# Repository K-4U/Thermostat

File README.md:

Thermostat
==========

This project will be able to replace a standard Thermostat hanging on your wall. The project is **not** suitable for [OpenTherm](http://en.wikipedia.org/wiki/OpenTherm "OpenTherm").

For now, the project is only an idea.

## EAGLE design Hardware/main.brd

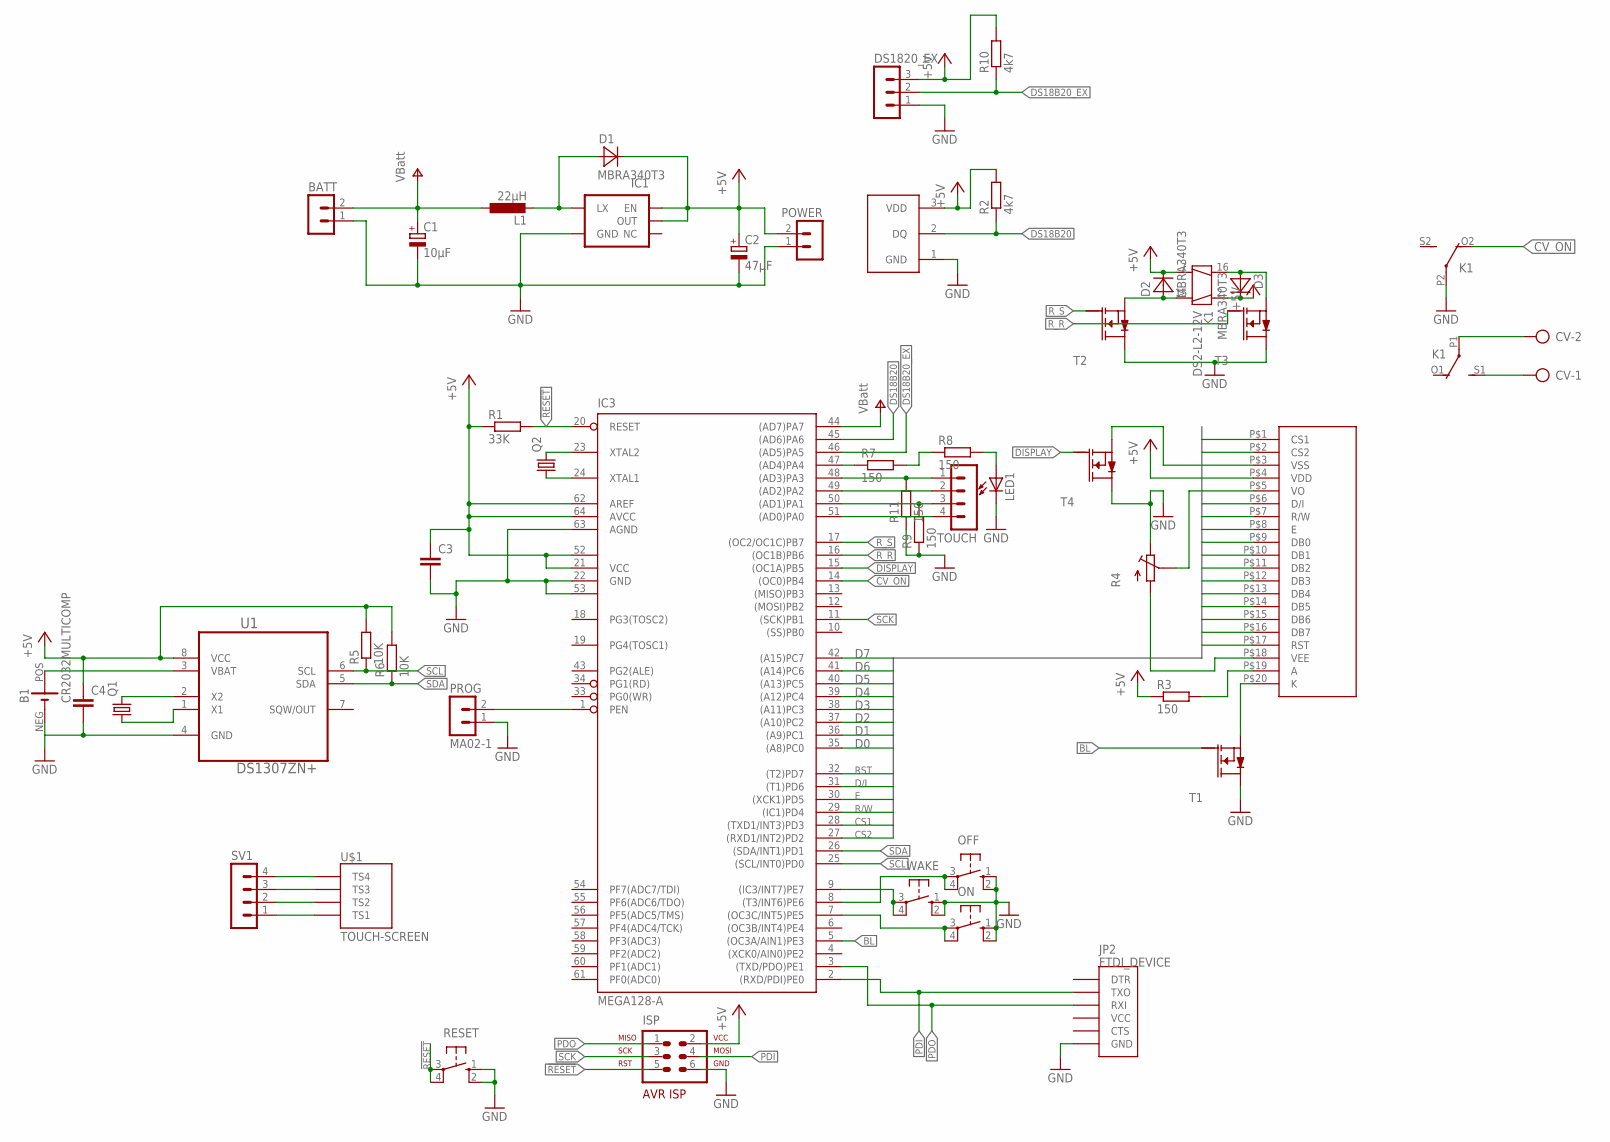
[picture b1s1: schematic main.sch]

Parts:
B1: CR2032MULTICOMP; CR2032
BATT: MA02-1
C1: 10µF; PANASONIC_D
C2: 47µF; PANASONIC_D
C3, C4: C-EUC0805; C0805
CV: AK300/2
D1, D2, D3: MBRA340T3; SMA
DS1820: DS18B20; TO92
DS1820_EX: MA03-1
IC1: V_REG_NCP1400SOT23-5; SOT23-5
IC3: MEGA128-A; TQFP64
ISP: AVR-ISP-6HORZ; AVR-ISP-6R
JP2: FTDI_DEVICE; FTDI_DEVICE_SIDE
K1: DS2-L2-12V; DS2E-L2
L1: 22µH; L2012C
LED1: LEDSML1206; SML1206
OFF: 10-XX; B3F-10XX
ON: 10-XX; B3F-10XX; MPN B3F-1000
POWER: MA02-1
PROG: MA02-1
Q1: CRYSTALTC26V; TC26V
Q2: CRYSTALSM49; SM49
R1: 33K; R0805
R2, R10: 4k7; R0805
R3, R7, R8, R9, R11: 150; R0805
R4: TRIM
R5, R6: 10K; R0805
RESET: 10-XX; B3F-10XX
SV1: MA04-1
T1, T2, T3, T4: IRLML2502PBF; SOT23
TOUCH: MA04-1
U1: DS1307ZN+; SOIC127P600X175-8N
U$1: TOUCH-SCREEN
U$2: GLCD_LEDSEE
WAKE: 10-XX; B3F-10XX

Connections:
!RESET: IC3.20 (RESET), ISP.5, R1.2, RESET.3, RESET.4 (P1)
+5V: C2.+, C3.1, C4.1, D1.C, D2.C, D3.C, DS1820.3 (VDD), DS1820_EX.3, IC1.1 (EN), IC1.2 (OUT), IC3.21 (VCC), IC3.52 (VCC1), IC3.62 (AREF), IC3.64 (AVCC), ISP.2, K1.1 (2), K1.2 (3), POWER.2 (4), R1.1, R2.2, R3.1, R5.2, R6.2, R10.2, U1.8 (VCC), U$2.P$4 (VDD)
BL: IC3.5 ((OC3A/AIN1)PE3), T1.1 (G)
CS1: IC3.28 ((TXD1/INT3)PD3), U$2.P$1 (CS1)
CS2: IC3.27 ((RXD1/INT2)PD2), U$2.P$2 (CS2)
CV_ON: IC3.14 ((OC0)PB4), K1.O2 (O)
D0: IC3.35 ((A8)PC0), U$2.P$9 (DB0)
D1: IC3.36 ((A9)PC1), U$2.P$10 (DB1)
D2: IC3.37 ((A10)PC2), U$2.P$11 (DB2)
D3: IC3.38 ((A11)PC3), U$2.P$12 (DB3)
D4: IC3.39 ((A12)PC4), U$2.P$13 (DB4)
D5: IC3.40 ((A13)PC5), U$2.P$14 (DB5)
D6: IC3.41 ((A14)PC6), U$2.P$15 (DB6)
D7: IC3.42 ((A15)PC7), U$2.P$16 (DB7)
D/I: IC3.31 ((T1)PD6), U$2.P$6 (D/I)
DISPLAY: IC3.15 ((OC1A)PB5), T4.1 (G)
DS18B20: DS1820.2 (DQ), IC3.45 ((AD6)PA6), R2.1
DS18B20_EX: DS1820_EX.2, IC3.46 ((AD5)PA5), R10.1
E: IC3.30 ((XCK1)PD5), U$2.P$8 (E)
GND: B1.NEG (-), BATT.1 (3), C1.-, C2.-, C3.2, C4.2, DS1820.1 (GND), DS1820_EX.1, IC1.4 (GND), IC3.22 (GND), IC3.53 (GND1), IC3.63 (AGND), ISP.6, JP2.P$6 (GND), K1.P2, LED1.C, OFF.1 (S), OFF.2 (S1), ON.1 (S), ON.2 (S1), POWER.1 (3), PROG.1 (3), R4.1, R9.1, R11.1, RESET.1 (S), RESET.2 (S1), T1.3 (D), T2.3 (D), T3.3 (D), T4.3 (D), U1.4 (GND), WAKE.1 (S), WAKE.2 (S1)
unnamed: D1.A, IC1.5 (LX), L1.2
unnamed: SV1.4, U$1.P$1 (TS4)
unnamed: SV1.3, U$1.P$2 (TS3)
unnamed: SV1.2, U$1.P$3 (TS2)
unnamed: SV1.1, U$1.P$4 (TS1)
unnamed: R3.2, U$2.P$19 (A)
unnamed: IC3.1 (PEN), PROG.2 (4)
unnamed: T1.2 (S), U$2.P$20 (K)
unnamed: IC3.9 ((IC3/INT7)PE7), WAKE.3, WAKE.4 (P1)
unnamed: R4.3, U$2.P$18 (VEE)
unnamed: R4.2 (T), U$2.P$5 (VO)
unnamed: D2.A, K1.15 (4), T2.2 (S)
unnamed: D3.A, K1.16 (1), T3.2 (S)
unnamed: IC3.8 ((T3/INT6)PE6), OFF.3, OFF.4 (P1)
unnamed: CV.2, K1.P1
unnamed: CV.1, K1.S1 (S)
unnamed: IC3.51 ((AD0)PA0), TOUCH.4
unnamed: IC3.50 ((AD1)PA1), R9.2, TOUCH.3
unnamed: IC3.49 ((AD2)PA2), TOUCH.2
unnamed: IC3.48 ((AD3)PA3), R11.2, TOUCH.1
unnamed: T4.2 (S), U$2.P$3 (VSS)
unnamed: B1.POS (+), U1.3 (VBAT)
unnamed: Q1.1, U1.1 (X1)
unnamed: Q1.2, U1.2 (X2)
unnamed: IC3.7 ((OC3C/INT5)PE5), ON.3, ON.4 (P1)
unnamed: LED1.A, R8.2
unnamed: IC3.47 ((AD4)PA4), R7.1
unnamed: R7.2, R8.1
unnamed: IC3.23 (XTAL2), Q2.2
unnamed: IC3.24 (XTAL1), Q2.1
PDI: IC3.2 ((RXD/PDI)PE0), ISP.4, JP2.P$2 (TXO)
PDO: IC3.3 ((TXD/PDO)PE1), ISP.1, JP2.P$3 (RXI)
R/W: IC3.29 ((IC1)PD4), U$2.P$7 (R/W)
RST: IC3.32 ((T2)PD7), U$2.P$17 (RST)
R_R: IC3.16 ((OC1B)PB6), T3.1 (G)
R_S: IC3.17 ((OC2/OC1C)PB7), T2.1 (G)
SCK: IC3.11 ((SCK)PB1), ISP.3
SCL: IC3.25 ((SCL/INT0)PD0), R5.1, U1.6 (SCL)
SDA: IC3.26 ((SDA/INT1)PD1), R6.1, U1.5 (SDA)
V+: BATT.2 (4), C1.+, IC3.44 ((AD7)PA7), L1.1

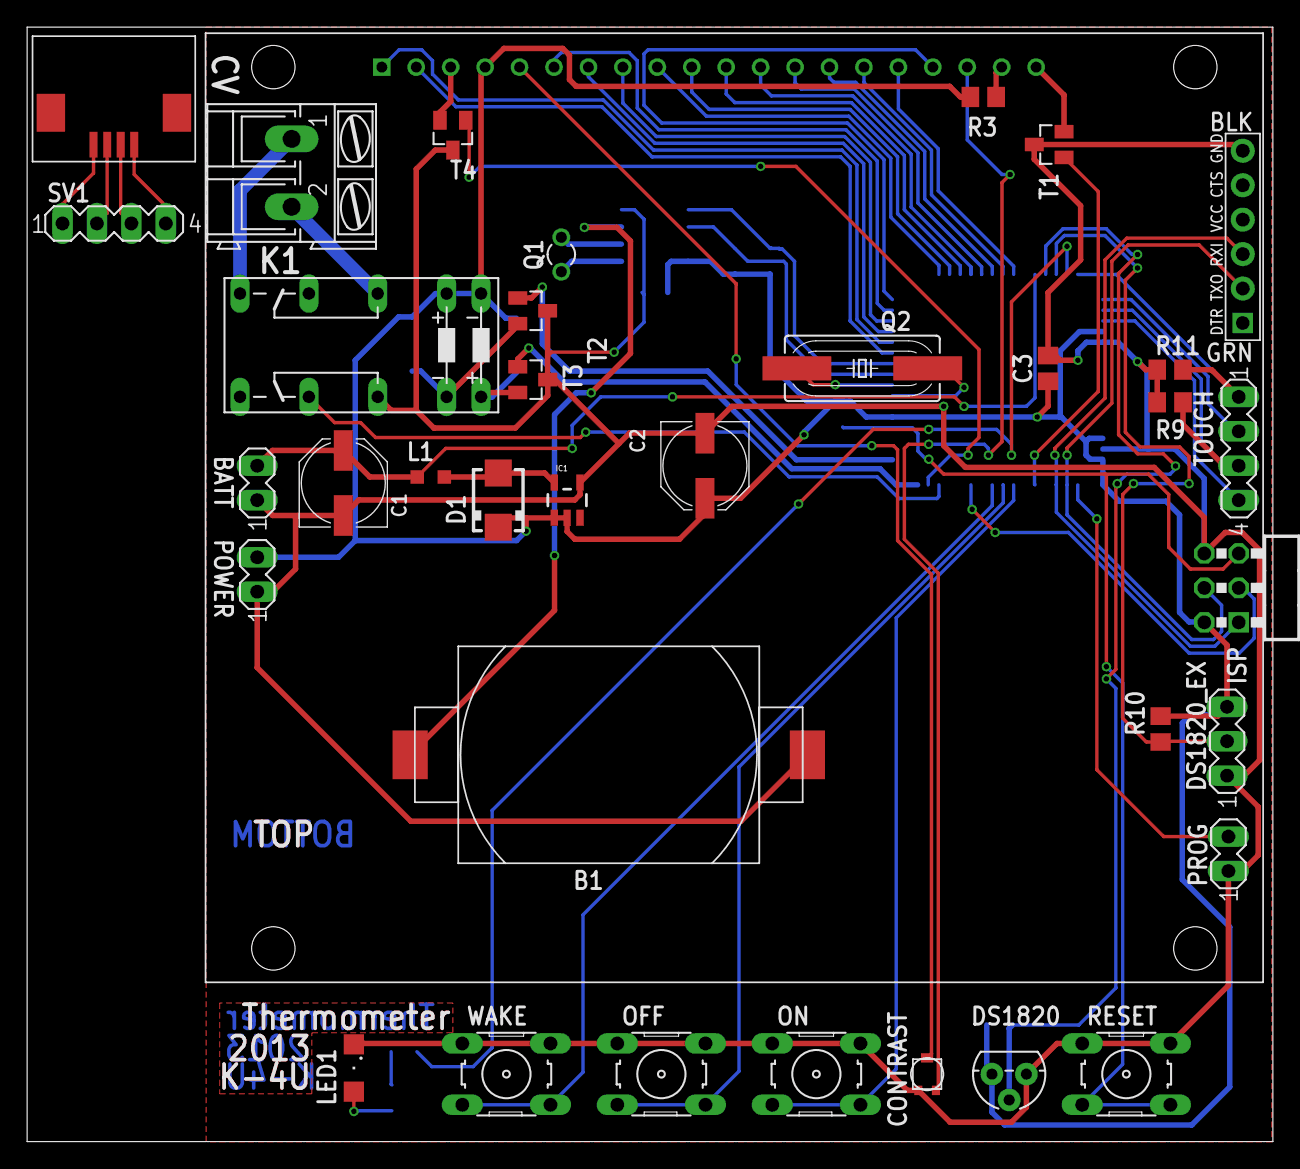
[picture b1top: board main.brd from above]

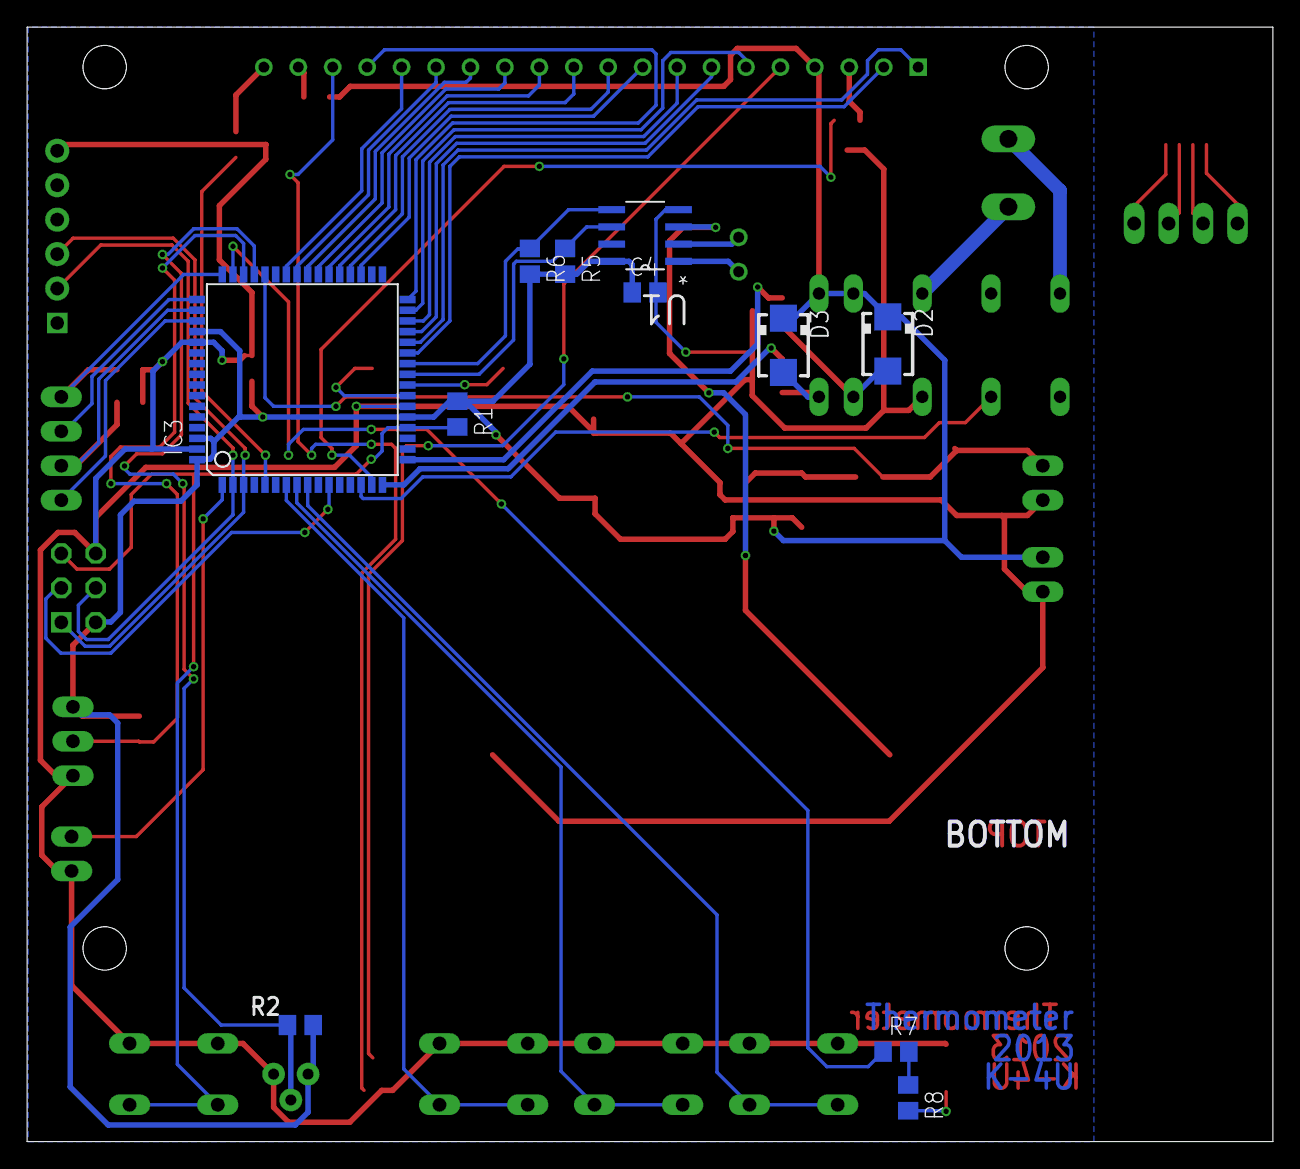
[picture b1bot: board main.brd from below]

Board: 2 copper layers, 91.9 x 82.2 mm, 47 parts (11 on the bottom side), 60 nets.

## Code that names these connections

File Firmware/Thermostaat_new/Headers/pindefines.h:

/*
 * pindefines.h
 *
 * Created: 7-2-2013 15:26:12
 *  Author: Koen Beckers
 */ 


#ifndef PINDEFINES_H_
#define PINDEFINES_H_

#define DDR_LCD				DDRC
#define PORT_LCD			PORTC
#define LCD					_BV(PC2)

#define DDR_LED				DDRA
#define PORT_LED			PORTA
#define LED					_BV(PA4)

#define PORT_LCD_CMD		PORTD
#define DDR_LCD_CMD			DDRD
#define LCD_CMD_DI			PD4
#define LCD_CMD_RW			PD5
#define LCD_CMD_EN			PD6
#define LCD_CMD_CS1			PD3
#define LCD_CMD_CS2			PD2

#define PORT_BACKLIGHT		PORTD
#define DDR_BACKLIGHT		DDRD
#define BACKLIGHT			_BV(PD7)
#define PWM_BACKLIGHT		OCR2A

#define PIN_LCD_DATA		PINB
#define PORT_LCD_DATA		PORTB
#define DDR_LCD_DATA		DDRB

#define PORT_TOUCH			PORTA
#define PIN_TOUCH			PINA
#define DDR_TOUCH			DDRA
#define TOUCH_1				PA0
#define TOUCH_2				PA1
#define TOUCH_3				PA2
#define TOUCH_4				PA3

#define ADC_BATTERY			PA5


#define DDR_CVP				DDRC
#define PORT_CVP			PORTC
#define CVP_ON				_BV(PC7)
#define CVP_OFF				_BV(PC6)

#define DDR_BUTTONS			DDRC
#define PORT_BUTTONS		PORTC
#define PIN_BUTTONS			PINC
#define BUTTON_WAKE			_BV(PC3)
#define BUTTON_ON			_BV(PC4)
#define BUTTON_OFF			_BV(PC5)

#define TEMP_INTERN			_BV(PA6)
#define PIN_TEMP_INTERN		PINA
#define PORT_TEMP_INTERN	PORTA
#define DDR_TEMP_INTERN		DDRA

#define TEMP_EXTERN			_BV(PA7)
#define PIN_TEMP_EXTERN		PINA
#define PORT_TEMP_EXTERN	PORTA
#define DDR_TEMP_EXTERN		DDRA





#endif /* PINDEFINES_H_ */

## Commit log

2013-01-30 Added schematic, PCB and BOM
2013-01-30 Added a ds1307
2013-01-31 Rotated the PCB, Added a button + LED
2013-01-31 GLCD now working. Test firmware
2013-02-02 Partially working firmware. It's just a test
2013-02-02 New UI. A lot cleaner now!
2013-02-03 Presets added, time added, CV added
2013-02-10 Added some extra components + bigger PCB
2013-02-10 Code in a new style
2013-02-12 Added the image converter
2013-02-12 Added new firmware
2013-02-13 This pcb version has been send to seeed.
2013-03-15 Added PDF's
2013-03-17 New programming header

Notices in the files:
parts and their libraries:
SparkFun-PowerIC: Licensing: CC v3.0 Share-Alike You are welcome to use this library for commercial purposes.
